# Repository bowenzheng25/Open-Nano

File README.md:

# Open Nano

This repository describes how to build and use your own nanopositioner. 

## Getting Started

1.  Go over this readme file for high-level overview
2.  Obtain the parts listed in the [Bill of Materials](https://github.com/bwnzhng/Open-Nano/blob/main/assembly/bom.md)
3.  Assemble the instrument and electronics
4.  Configure the hardware to fit your needs
5.  Upload firmware using VSCode with PlattformIO plugin
6.  Calibrate axis

## Design Files

Files (ie .stl and .dxf) for your reproduction are saved in [the assembly folder](https://github.com/bwnzhng/Open-Nano/tree/main/assembly/cad)

The CAD files are produced in Fusion360. You can get free access through the educational license. 

Otherwise, engineering drawings are attached for you to reproduce the part in your choice of CAD software as the designs are relatively straightforward.

## Electronics

The PCB schematics are designed in KICAD. No SMD soldering is required since through hole electronic components are used for easier hands-on assembly.

Please note you will need to attach heatsinks to the amplifiers to maintain optimal performance.

This repository also contains fabrication files that can directly uploaded to a PCB manufacturer (located in [the electronics folder](https://github.com/bwnzhng/Open-Nano/tree/main/electronics))

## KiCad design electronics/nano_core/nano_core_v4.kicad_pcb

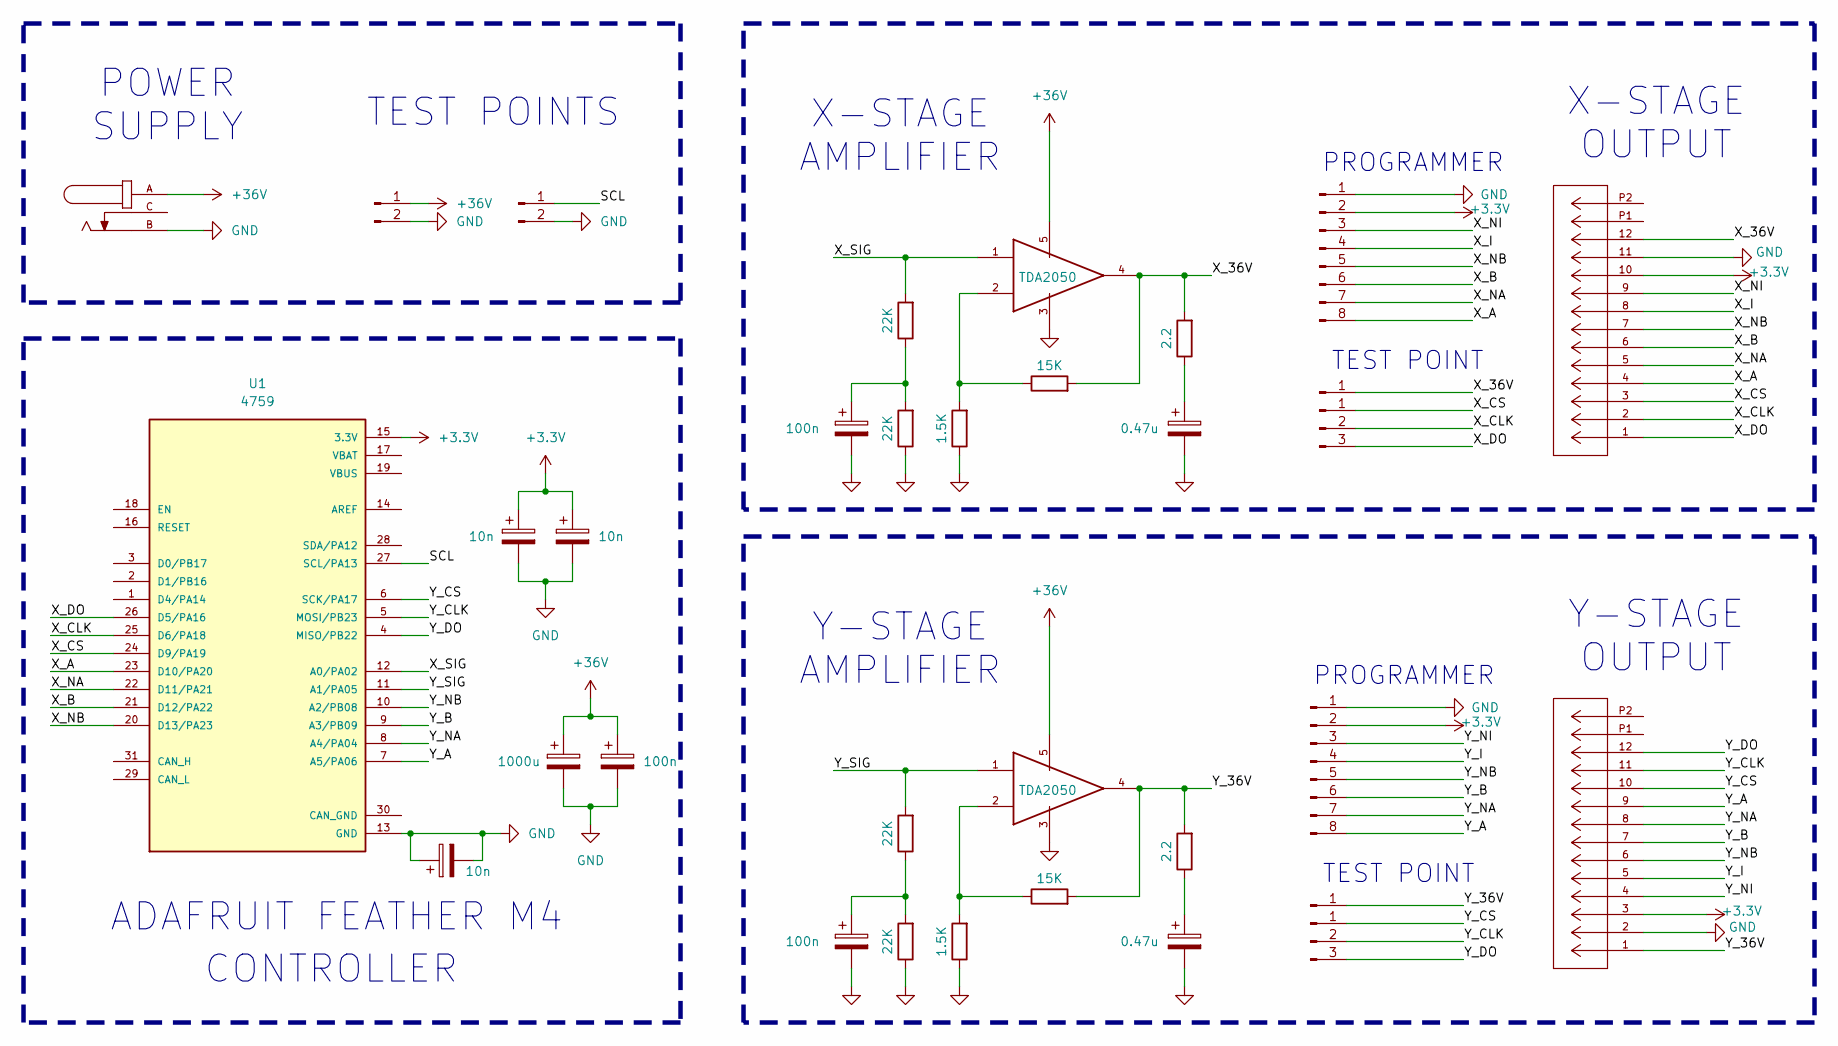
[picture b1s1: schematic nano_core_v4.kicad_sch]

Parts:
C1: 1000u; R_Axial_DIN0204_L3.6mm_D1.6mm_P5.08mm_Horizontal
C2, C4, C5: 100n; R_Axial_DIN0204_L3.6mm_D1.6mm_P5.08mm_Horizontal
C3, C8: 0.47u; R_Axial_DIN0204_L3.6mm_D1.6mm_P5.08mm_Horizontal
C9, C10, C11: 10n; R_Axial_DIN0204_L3.6mm_D1.6mm_P5.08mm_Horizontal
J1, J11: Conn_01x02_Pin; PinHeader_1x02_P2.54mm_Vertical
J2, J3: 2005280120; CON_2005280120_MOL; MANUFACTURER_PART_NUMBER 2005280120
J4, J5: Conn_01x08_Pin; PinHeader_1x08_P2.54mm_Vertical
J6: 54-00166; TENSILITY_54-00166; PARTREV A
J7, J9: Conn_01x01_Pin; PinHeader_1x01_P1.00mm_Vertical
J8, J10: Conn_01x03_Pin; PinHeader_1x03_P1.00mm_Vertical
R1, R9: 15K; R_Axial_DIN0204_L3.6mm_D1.6mm_P5.08mm_Horizontal
R2, R10: 2.2; R_Axial_DIN0204_L3.6mm_D1.6mm_P5.08mm_Horizontal
R3, R8: 1.5K; R_Axial_DIN0204_L3.6mm_D1.6mm_P5.08mm_Horizontal
R4, R5, R6, R7: 22K; R_Axial_DIN0204_L3.6mm_D1.6mm_P5.08mm_Horizontal
U1: 4759; MODULE_4759; PARTREV Dec. 08 2020
U2, U3: TDA2050; PENTAWATT

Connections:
+3.3V: C10.1, C11.1, J2.10, J3.3, J4.2, J5.2, U1.15 (3.3V)
+36V: C1.1, C2.1, J1.1, J6.A, U2.5 (SUPPLY_VOLTAGE), U3.5 (SUPPLY_VOLTAGE)
/SCL: J11.1, U1.27 (SCL/PA13)
/X_36V: J2.12, J7.1 (Pin_1_1), R1.2, R2.2, U2.4 (OUTPUT)
/X_A: J2.4, J4.8, U1.23 (D10/PA20)
/X_B: J2.6, J4.6, U1.21 (D12/PA22)
/X_CLK: J2.2, J8.2, U1.25 (D6/PA18)
/X_CS: J2.3, J8.1, U1.24 (D9/PA19)
/X_DO: J2.1, J8.3, U1.26 (D5/PA16)
/X_I: J2.8, J4.4
/X_NA: J2.5, J4.7, U1.22 (D11/PA21)
/X_NB: J2.7, J4.5, U1.20 (D13/PA23)
/X_NI: J2.9, J4.3
/X_SIG: R5.2, U1.12 (A0/PA02), U2.1 (NONINVERTING)
/Y_36V: J3.1, J9.1 (Pin_1_1), R9.2, R10.2, U3.4 (OUTPUT)
/Y_A: J3.9, J5.8, U1.7 (A5/PA06)
/Y_B: J3.7, J5.6, U1.9 (A3/PB09)
/Y_CLK: J3.11, J10.2, U1.5 (MOSI/PB23)
/Y_CS: J3.10, J10.1, U1.6 (SCK/PA17)
/Y_DO: J3.12, J10.3, U1.4 (MISO/PB22)
/Y_I: J3.5, J5.4
/Y_NA: J3.8, J5.7, U1.8 (A4/PA04)
/Y_NB: J3.6, J5.5, U1.10 (A2/PB08)
/Y_NI: J3.4, J5.3
/Y_SIG: R6.2, U1.11 (A1/PA05), U3.1 (NONINVERTING)
GND: C1.2, C2.2, C3.2, C4.2, C5.2, C8.2, C9.1, C9.2, C10.2, C11.2, J1.2, J2.11, J3.2, J4.1, J5.1, J6.B, J11.2, R3.1, R4.1, R7.1, R8.1, U1.13 (GND), U2.3 (GND), U3.3 (GND)
unnamed: C3.1, R2.1
unnamed: C4.1, R4.2, R5.1
unnamed: C5.1, R6.1, R7.2
unnamed: C8.1, R10.1
unnamed: R1.1, R3.2, U2.2 (INVERTING)
unnamed: R8.2, R9.1, U3.2 (INVERTING)

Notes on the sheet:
Y-STAGE AMPLIFIER
Y-STAGE OUTPUT
CONTROLLER
PROGRAMMER
TEST POINT
TEST POINTS
POWER SUPPLY
X-STAGE OUTPUT
X-STAGE AMPLIFIER
ADAFRUIT FEATHER M4

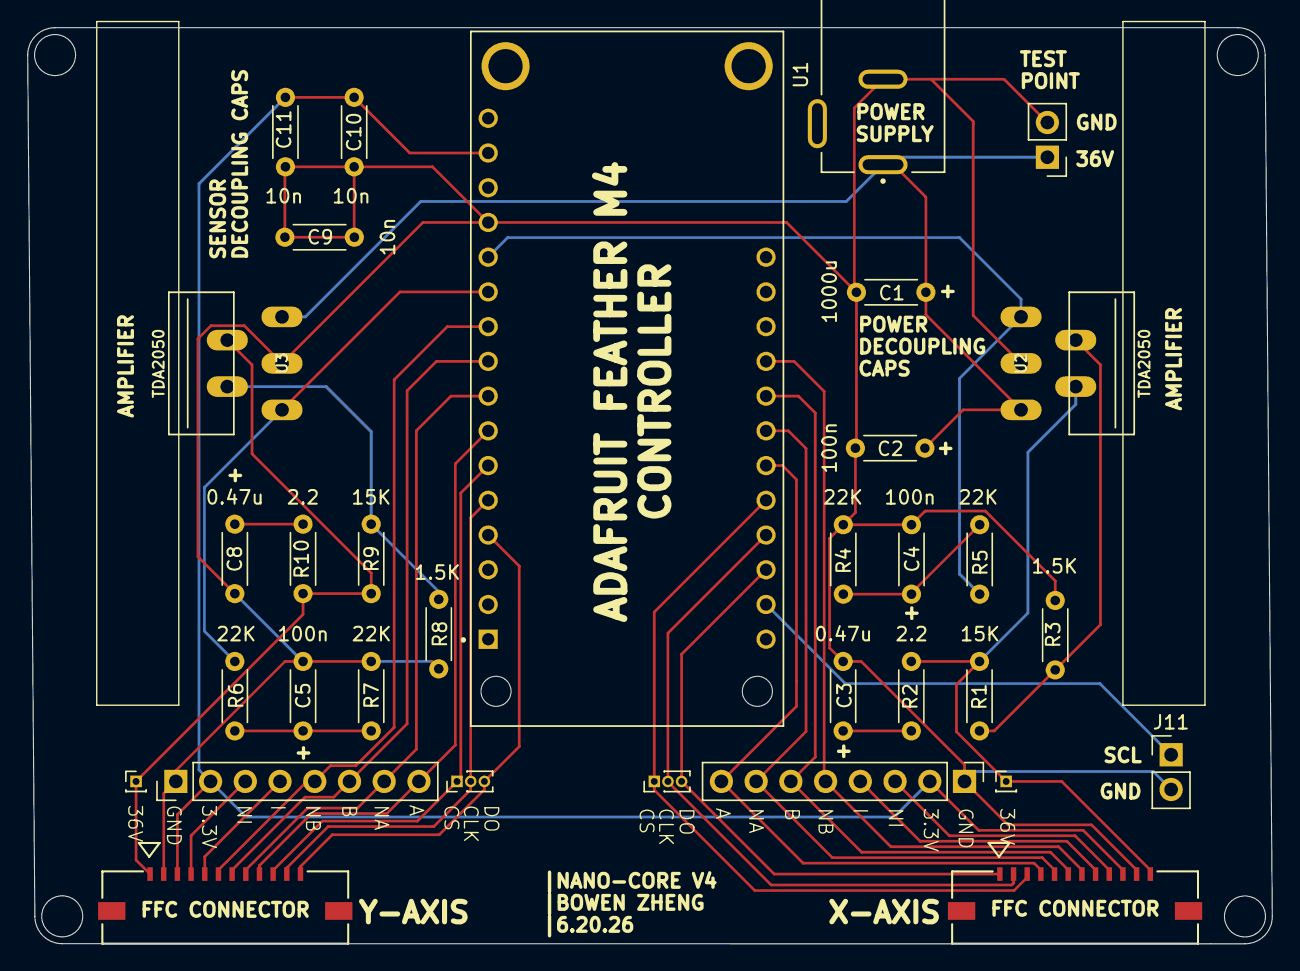
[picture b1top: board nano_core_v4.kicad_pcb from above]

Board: 2 copper layers, 91.0 x 67.0 mm, 33 parts (0 on the bottom side), 32 nets.

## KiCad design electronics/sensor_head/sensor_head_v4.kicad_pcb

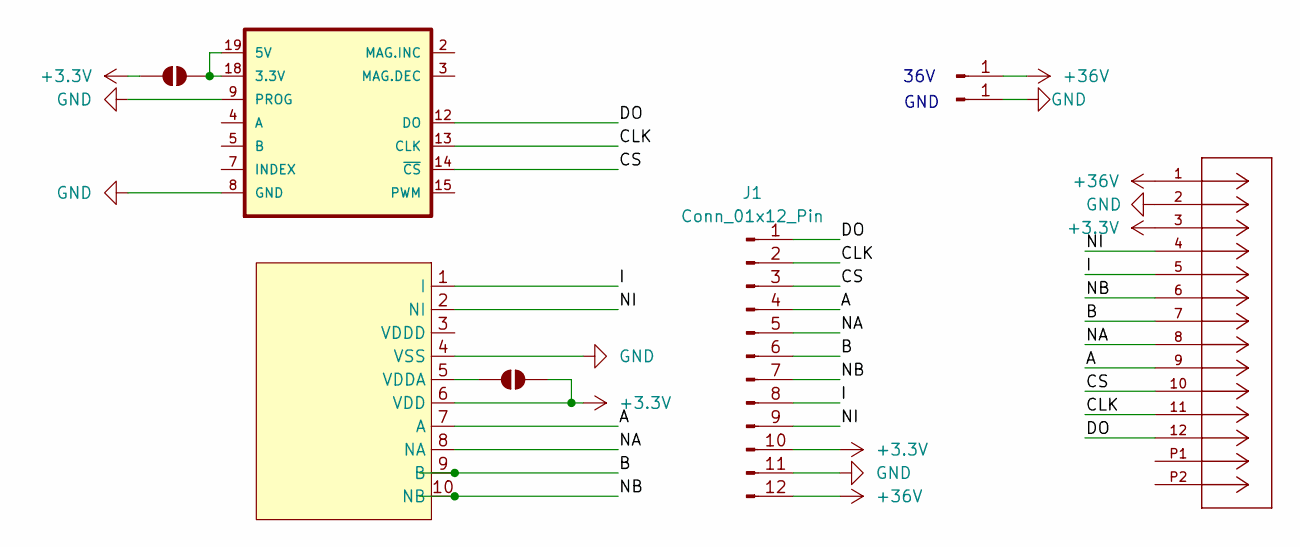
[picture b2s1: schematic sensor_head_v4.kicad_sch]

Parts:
J1: Conn_01x12_Pin; PinHeader_1x12_P1.00mm_Vertical
J2: 2005280120; CON_2005280120_MOL; MANUFACTURER_PART_NUMBER 2005280120
J3, J4: Conn_01x01_Pin; PinHeader_1x01_P2.54mm_Vertical
JP3, JP4: SolderJumper_2_Open; SolderJumper-2_P1.3mm_Open_RoundedPad1.0x1.5mm
U3: AS5311; TSSOP.20
U4: posic_1030

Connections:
+3.3V: J1.10, J2.3, JP3.1 (A), JP4.2 (B), U4.6 (VDD)
+36V: J1.12, J2.1, J3.1 (Pin_1_1)
/A: J1.4, J2.9, U4.7 (A)
/B: J1.6, J2.7, U4.9 (B)
/CLK: J1.2, J2.11, U3.13 (CLK)
/CS: J1.3, J2.10, U3.14 (~CS)
/DO: J1.1, J2.12, U3.12 (DO)
/I: J1.8, J2.5, U4.1 (I)
/NA: J1.5, J2.8, U4.8 (NA)
/NB: J1.7, J2.6, U4.10 (NB)
/NI: J1.9, J2.4, U4.2 (NI)
GND: J1.11, J2.2, J4.1 (Pin_1_1), U3.8 (GND), U3.9 (PROG), U4.4 (VSS)
unnamed: JP3.2 (B), U3.18 (3.3V), U3.19 (5V)
unnamed: JP4.1 (A), U4.5 (VDDA)

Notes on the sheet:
GND
36V

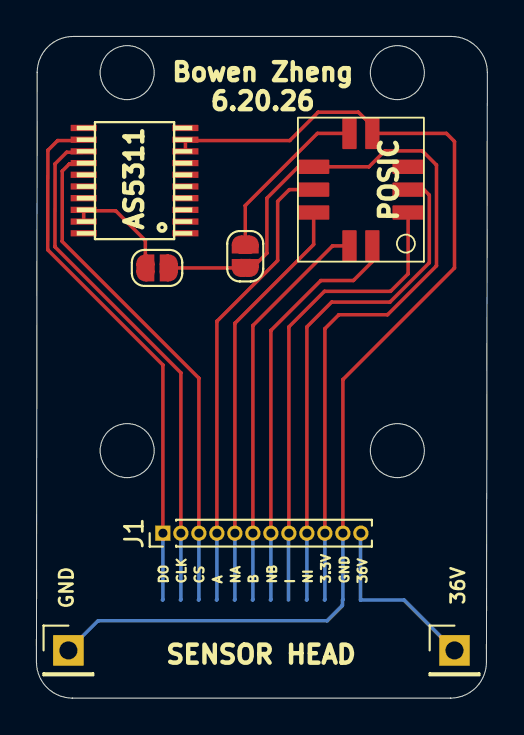
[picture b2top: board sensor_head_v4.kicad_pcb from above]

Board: 2 copper layers, 25.1 x 36.8 mm, 8 parts (1 on the bottom side), 14 nets.

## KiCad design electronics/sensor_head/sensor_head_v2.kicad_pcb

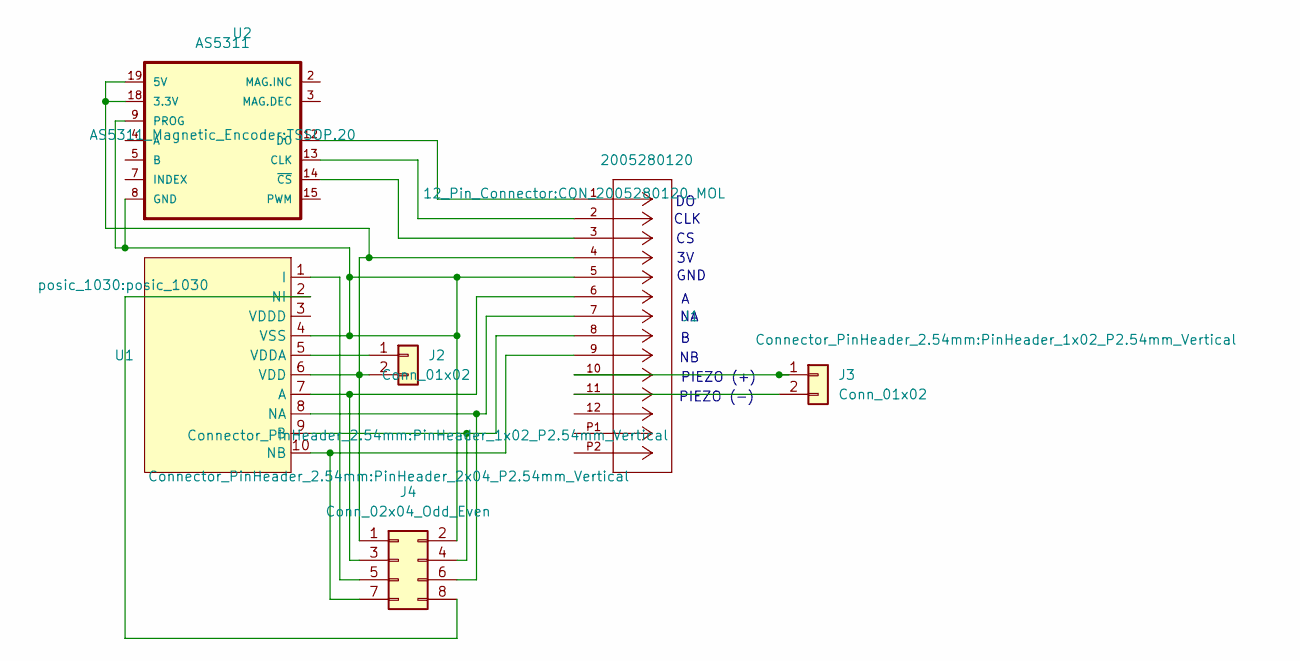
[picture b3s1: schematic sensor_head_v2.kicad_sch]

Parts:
J1: 2005280120; CON_2005280120_MOL; MANUFACTURER_PART_NUMBER 2005280120
J2, J3: Conn_01x02; PinHeader_1x02_P2.54mm_Vertical
J4: Conn_02x04_Odd_Even; PinHeader_2x04_P2.54mm_Vertical
U1: posic_1030
U2: AS5311; TSSOP.20

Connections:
unnamed: J2.1, U1.5 (VDDA)
unnamed: J1.4, J2.2, J4.1, U1.6 (VDD), U2.18 (3.3V), U2.19 (5V)
unnamed: J1.10, J3.1
unnamed: J1.11, J3.2
unnamed: J1.5, J4.2, U1.4 (VSS), U2.8 (GND), U2.9 (PROG)
unnamed: J1.6, J4.3, U1.7 (A)
unnamed: J1.8, J4.4, U1.9 (B)
unnamed: J4.5, U1.1 (I)
unnamed: J1.7, J4.6, U1.8 (NA)
unnamed: J1.9, J4.7, U1.10 (NB)
unnamed: J4.8, U1.2 (NI)
unnamed: J1.2, U2.13 (CLK)
unnamed: J1.1, U2.12 (DO)
unnamed: J1.3, U2.14 (~CS)

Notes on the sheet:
GND
PIEZO (+)
PIEZO (-)
CLK

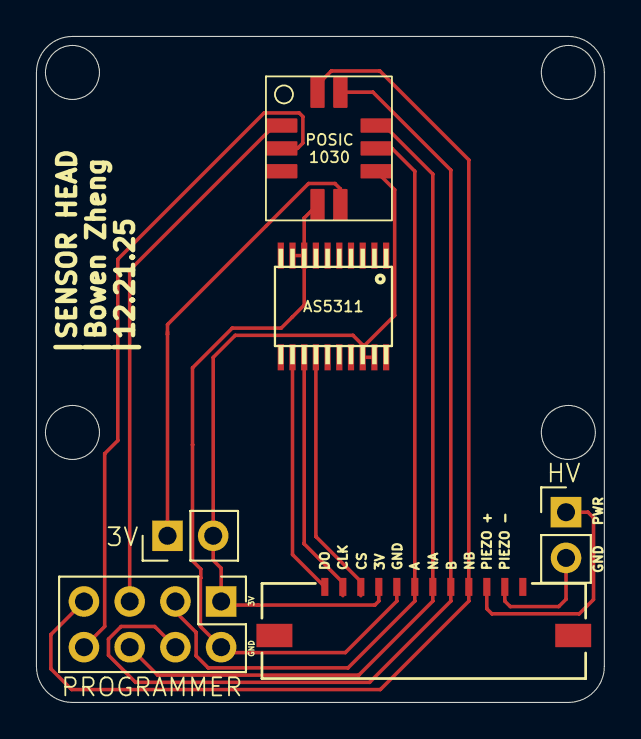
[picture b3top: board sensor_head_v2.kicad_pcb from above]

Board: 2 copper layers, 31.6 x 37.0 mm, 6 parts (0 on the bottom side), 14 nets.

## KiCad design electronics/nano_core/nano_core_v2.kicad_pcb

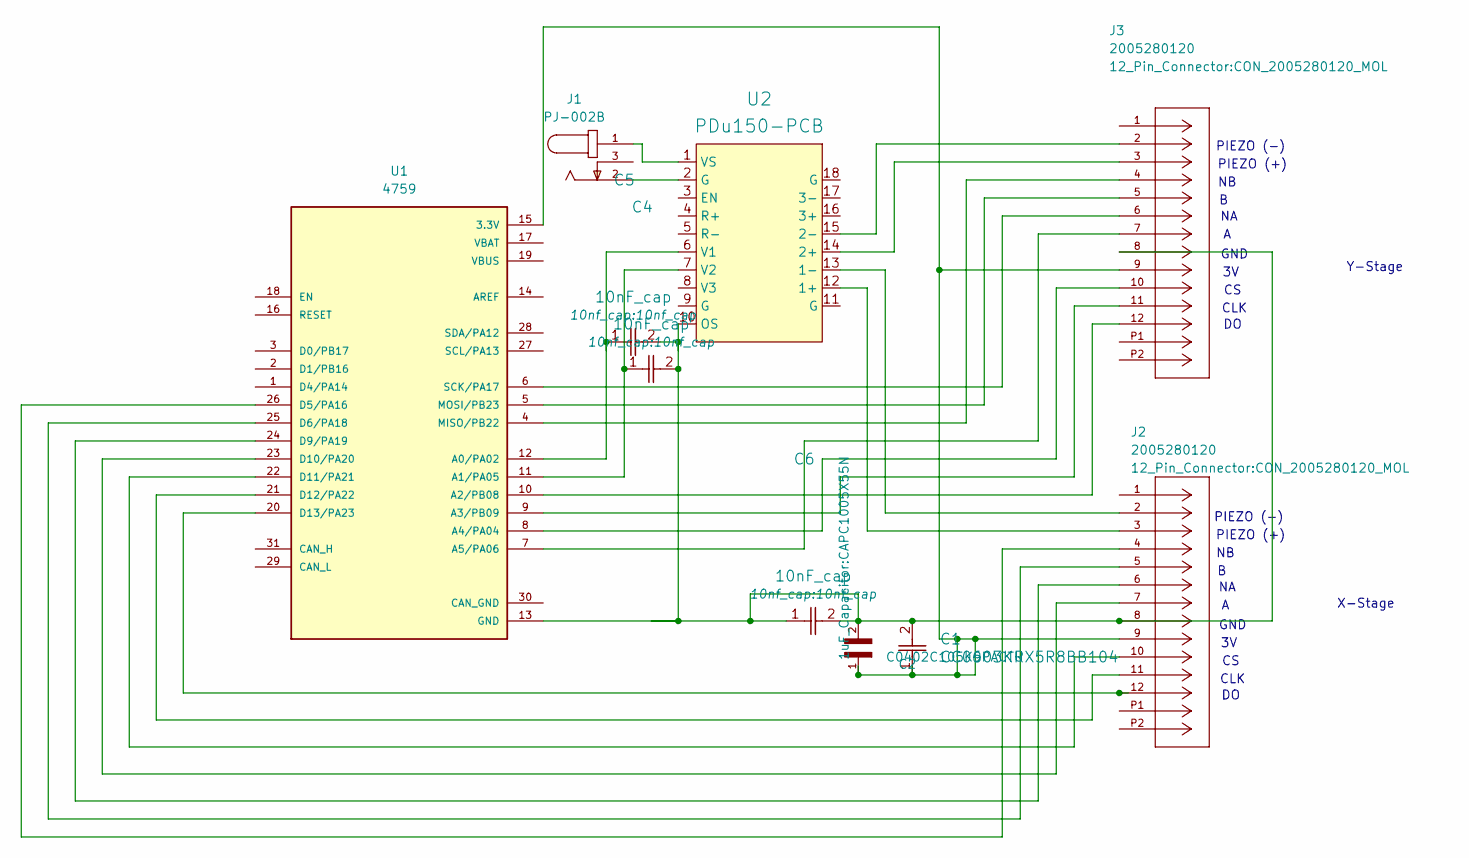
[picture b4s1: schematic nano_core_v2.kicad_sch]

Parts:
C1: CC0603KRX5R8BB104; CAP_CC0603KRX5R8BB104_YAG
C2: C0402C105K9PACTU; CAPC1005X55N; PARTREV N/A
C4, C5, C6: 10nF_cap; 10nf_cap
J1: PJ-002B; CUI_PJ-002B
J2, J3: 2005280120; CON_2005280120_MOL; MANUFACTURER_PART_NUMBER 2005280120
U1: 4759; MODULE_4759; PARTREV Dec. 08 2020
U2: PDu150-PCB

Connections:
unnamed: J1.2, U2.2 (G)
unnamed: C1.1, C2.1, J2.9, J3.9, U1.15 (3.3V)
unnamed: C5.1, U1.12 (A0/PA02), U2.6 (V1)
unnamed: C4.1, U1.11 (A1/PA05), U2.7 (V2)
unnamed: J3.12, U1.10 (A2/PB08)
unnamed: J3.11, U1.9 (A3/PB09)
unnamed: J3.10, U1.8 (A4/PA04)
unnamed: J3.7, U1.7 (A5/PA06)
unnamed: J2.4, U1.26 (D5/PA16)
unnamed: J2.5, U1.25 (D6/PA18)
unnamed: J2.6, U1.24 (D9/PA19)
unnamed: J2.7, U1.23 (D10/PA20)
unnamed: J2.10, U1.22 (D11/PA21)
unnamed: J2.11, U1.21 (D12/PA22)
unnamed: J2.12, U1.20 (D13/PA23)
unnamed: C1.2, C2.2, C4.2, C5.2, C6.1, C6.2, J2.8, J3.8, U1.13 (GND), U2.10 (OS)
unnamed: J3.4, U1.4 (MISO/PB22)
unnamed: J3.5, U1.5 (MOSI/PB23)
unnamed: J3.6, U1.6 (SCK/PA17)
unnamed: J2.3, U2.12 (1+)
unnamed: J2.2, U2.13 (1-)
unnamed: J3.3, U2.14 (2+)
unnamed: J3.2, U2.15 (2-)
unnamed: J1.1, U2.1 (VS)

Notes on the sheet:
CLK
PIEZO (+)
GND
Y-Stage
PIEZO (-)
X-Stage

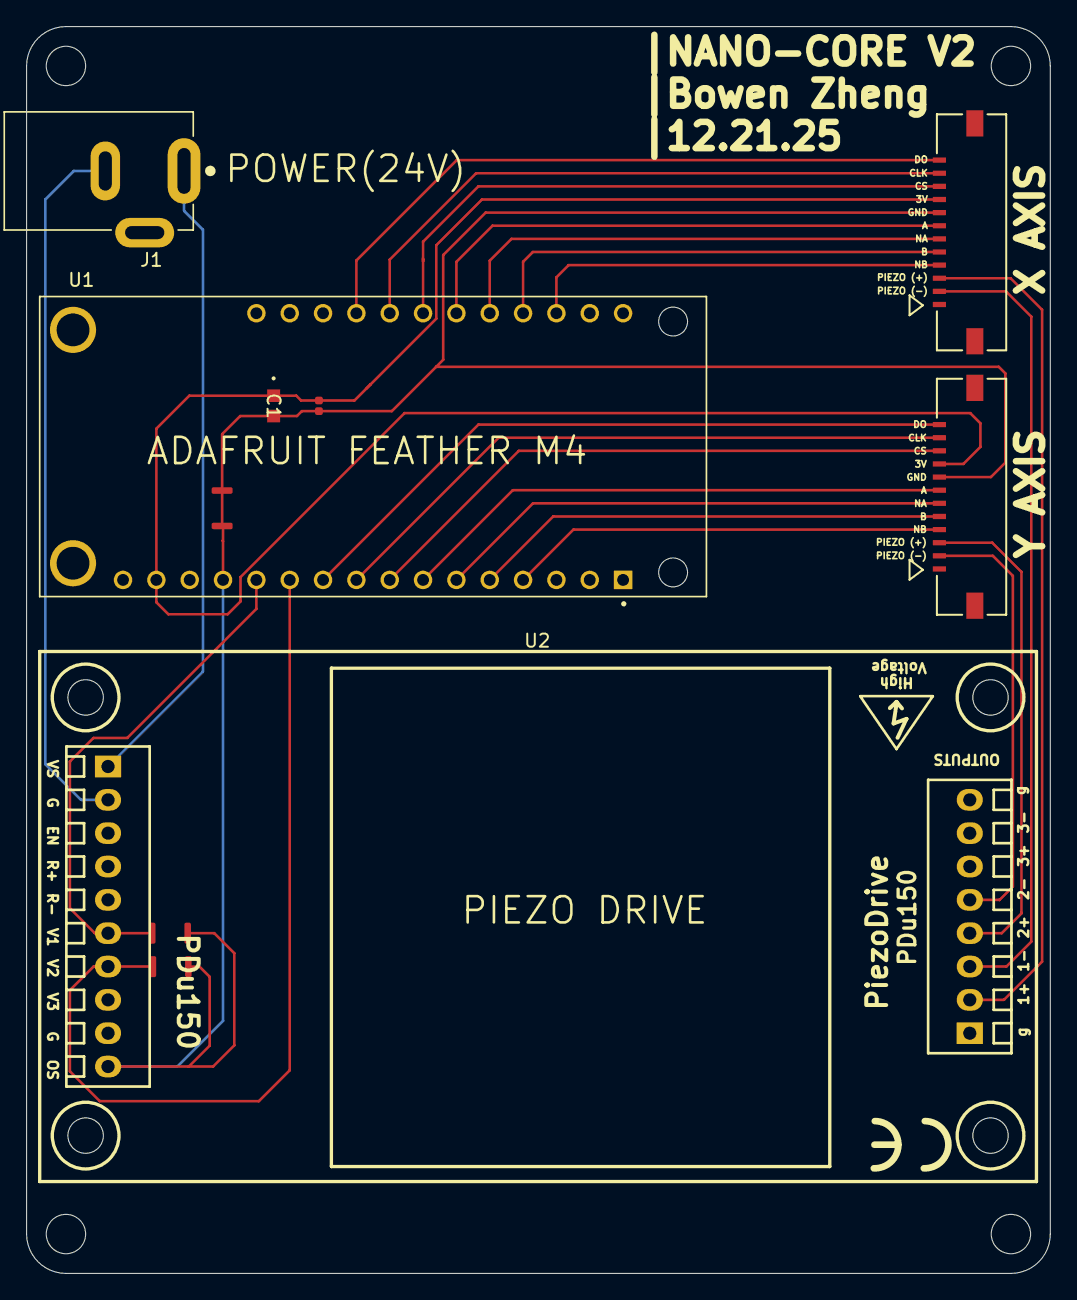
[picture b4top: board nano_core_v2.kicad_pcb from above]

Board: 2 copper layers, 78.0 x 95.0 mm, 10 parts (0 on the bottom side), 24 nets.

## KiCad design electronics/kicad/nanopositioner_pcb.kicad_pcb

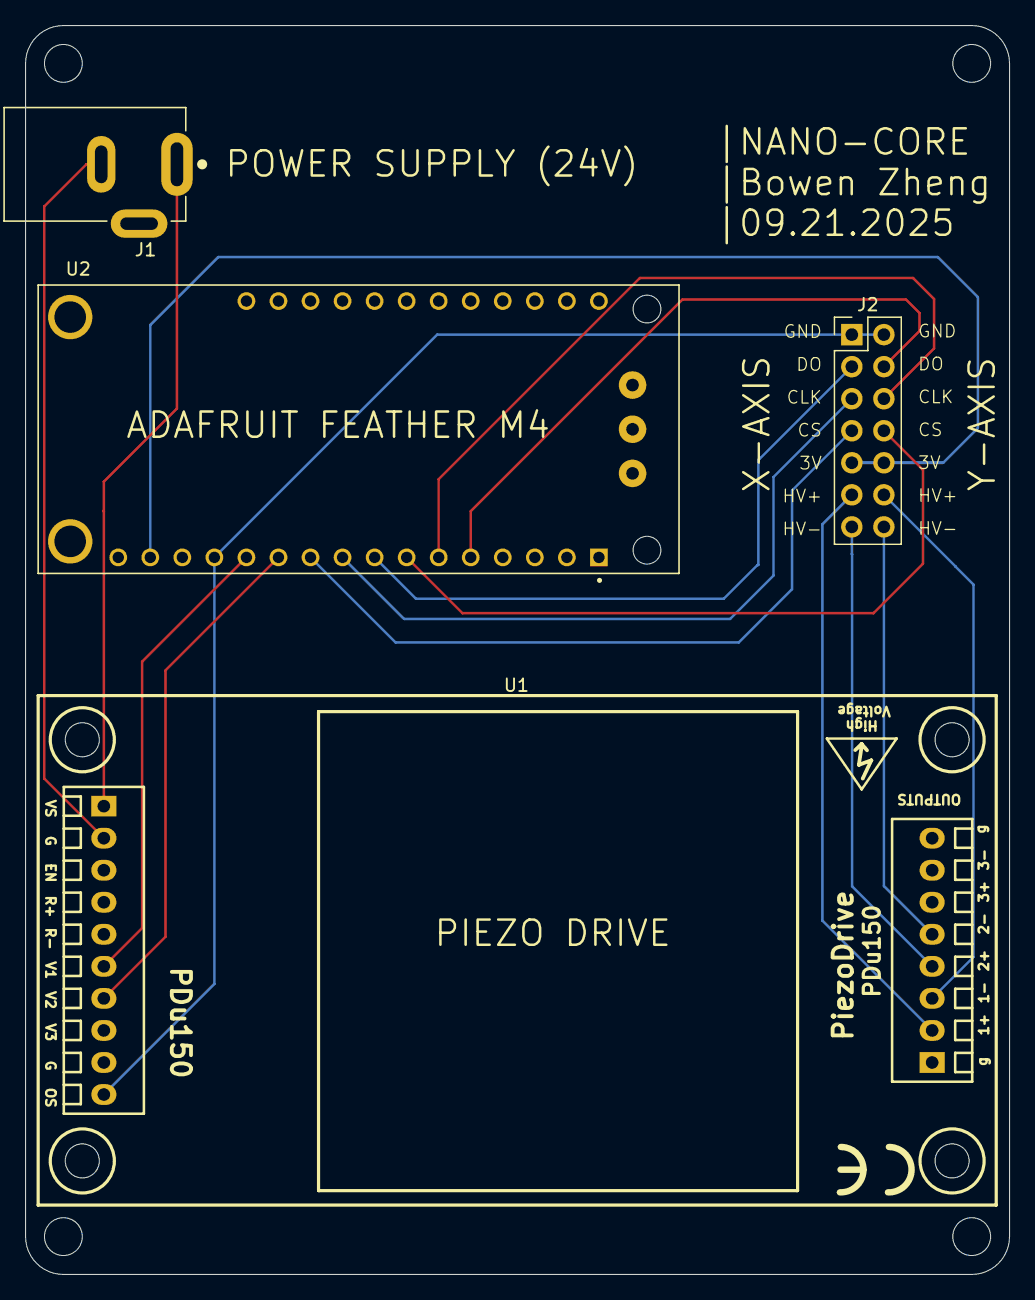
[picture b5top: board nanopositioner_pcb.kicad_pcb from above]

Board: 2 copper layers, 78.0 x 99.0 mm, 4 parts (0 on the bottom side), 16 nets.

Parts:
J1: PJ-002B; CUI_PJ-002B
J2: Conn_02x07_Odd_Even_MountingPin; PinHeader_2x07_P2.54mm_Vertical
U1: PDu150-PCB
U2: 4759; MODULE_4759

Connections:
unnamed: J1.2, U1.2 (G)
unnamed: J2.12, U1.13 (1-)
unnamed: J2.1, J2.2, U1.10 (OS), U2.13 (GND)
unnamed: J2.3, U2.8 (A4/PA04)
unnamed: J2.4, U2.5 (MOSI/PB23)
unnamed: J2.5, U2.9 (A3/PB09)
unnamed: J2.6, U2.6 (SCK/PA17)
unnamed: J2.7, U2.10 (A2/PB08)
unnamed: J2.8, U2.7 (A5/PA06)
unnamed: J2.9, J2.10, U2.15 (3.3V)
unnamed: J2.11, U1.12 (1+)
unnamed: J2.13, U1.14 (2+)
unnamed: J2.14, U1.15 (2-)
unnamed: U1.6 (V1), U2.12 (A0/PA02)
unnamed: U1.7 (V2), U2.11 (A1/PA05)
unnamed: J1.1, U1.1 (VS)

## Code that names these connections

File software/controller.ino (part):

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#define DEADBAND 1.0F

// MAGNETIC SENSOR INITIALIZATION
const int X_CS = A2;
const int X_CLK = A3;
const int X_DO = A4;
const int Y_CS = A5;
const int Y_CLK = 25;
const int Y_DO = 24;

// STATE MACHINE
const int CALIBRATE = 1;
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  setup_timers();

  // POSITION TRACKING
  pinMode(X_CS, OUTPUT);
  pinMode(X_CLK, OUTPUT);
  pinMode(X_DO, INPUT);
  pinMode(Y_CS, OUTPUT);
  pinMode(Y_CLK, OUTPUT);
  pinMode(Y_DO, INPUT);
  digitalWrite(X_CLK, 1);  //CLK
  digitalWrite(X_CS, 1);   //Csn
  digitalWrite(Y_CLK, 1);  //CLK
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
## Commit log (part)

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2025-11-02 Create user interface
2025-11-02 Add rest of user interface
2025-11-02 Create controller.ino for Adafruit Feather M4 Express
2025-11-02 Creating library for signal generation on adafruit microcontroller
2025-11-02 Add rest of signal generation library files
2025-11-03 Create electronics folder
2025-11-03 Created folder for jlc_pcb order
2025-11-03 Add files for jlc_pcb order
2025-11-03 Create kicad folder
2025-11-03 Add KICAD files
2025-11-03 Create components folder in cicada
2025-11-03 Electronic components (ie driver, power supply, microcontroller)
2025-11-03 Create cad and assembly file
2025-11-03 Create stl folder
2025-11-03 Added stl files of full CAD
2025-11-03 Create f3d files
2025-11-03 Add Fusion360 files of full CAD
2025-11-03 Create jlccnc order folder
2025-11-03 Drawings to upload for JLCCNC order
2025-11-03 Add bill of materials
2026-01-10 controller v2 pcb design in kicad
2026-01-10 sensor head v1 in kicad
2026-01-10 sensor_head v2 order for jlcpcb
2026-01-10 nano_core v2 order for jlcpcb
2026-02-02 Add sensor data processing and visualization script
    This script processes sensor data from Keyence and Arduino, identifies global extremes, selects turning points, and exports the processed data along with visualizations.
2026-02-02 Add sensor error processing and analysis script
    This script processes sensor data from Keyence and Arduino, calculates errors, and generates time domain and FFT analysis plots.
2026-02-02 Examples of collected data
2026-02-02 Add LowPass filter and sensor handling in Arduino sketch
    This commit introduces a LowPass filter class for signal processing in an Arduino sketch. It includes initialization of magnetic sensors, state machine logic, and methods for handling position tracki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
2026-02-27 Add resolution_test.ino for low pass filter implementation
2026-02-27 Add resolution_plot.py for sensor data visualization (paired with resolution_test.ino)
    This script imports sensor data, processes it, and generates plots for raw sensor data and mirror error analysis.
2026-02-28 Updated position tracking for robustness and update calibration range
    Added position tracking functionality and adjusted calibration parameters.
2026-03-01 Reduce NUM_COORDINATES and update coordinate values
2026-03-04 Update positioning logic (combining magnetic and posic encoder)
    Added a MovingAverage class for filtering and updated coordinate structure to include new fields for magnetic and positional counts. Adjusted the closed loop positioning function to accommodate the n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
2026-03-05 Only testing the posic encoder
    Updated state initialization and reduced NUM_COORDINATES. Modified coordinate values and adjusted limits and delays in various functions.
2026-03-27 Updated BOM
2026-03-28 Improved repeatability and accuracy performance
    Refactor state machine and coordinate handling in resolution_test.ino. Update encoder tracking and calibration parameters.
2026-03-28 Improved handling for LUT collection
